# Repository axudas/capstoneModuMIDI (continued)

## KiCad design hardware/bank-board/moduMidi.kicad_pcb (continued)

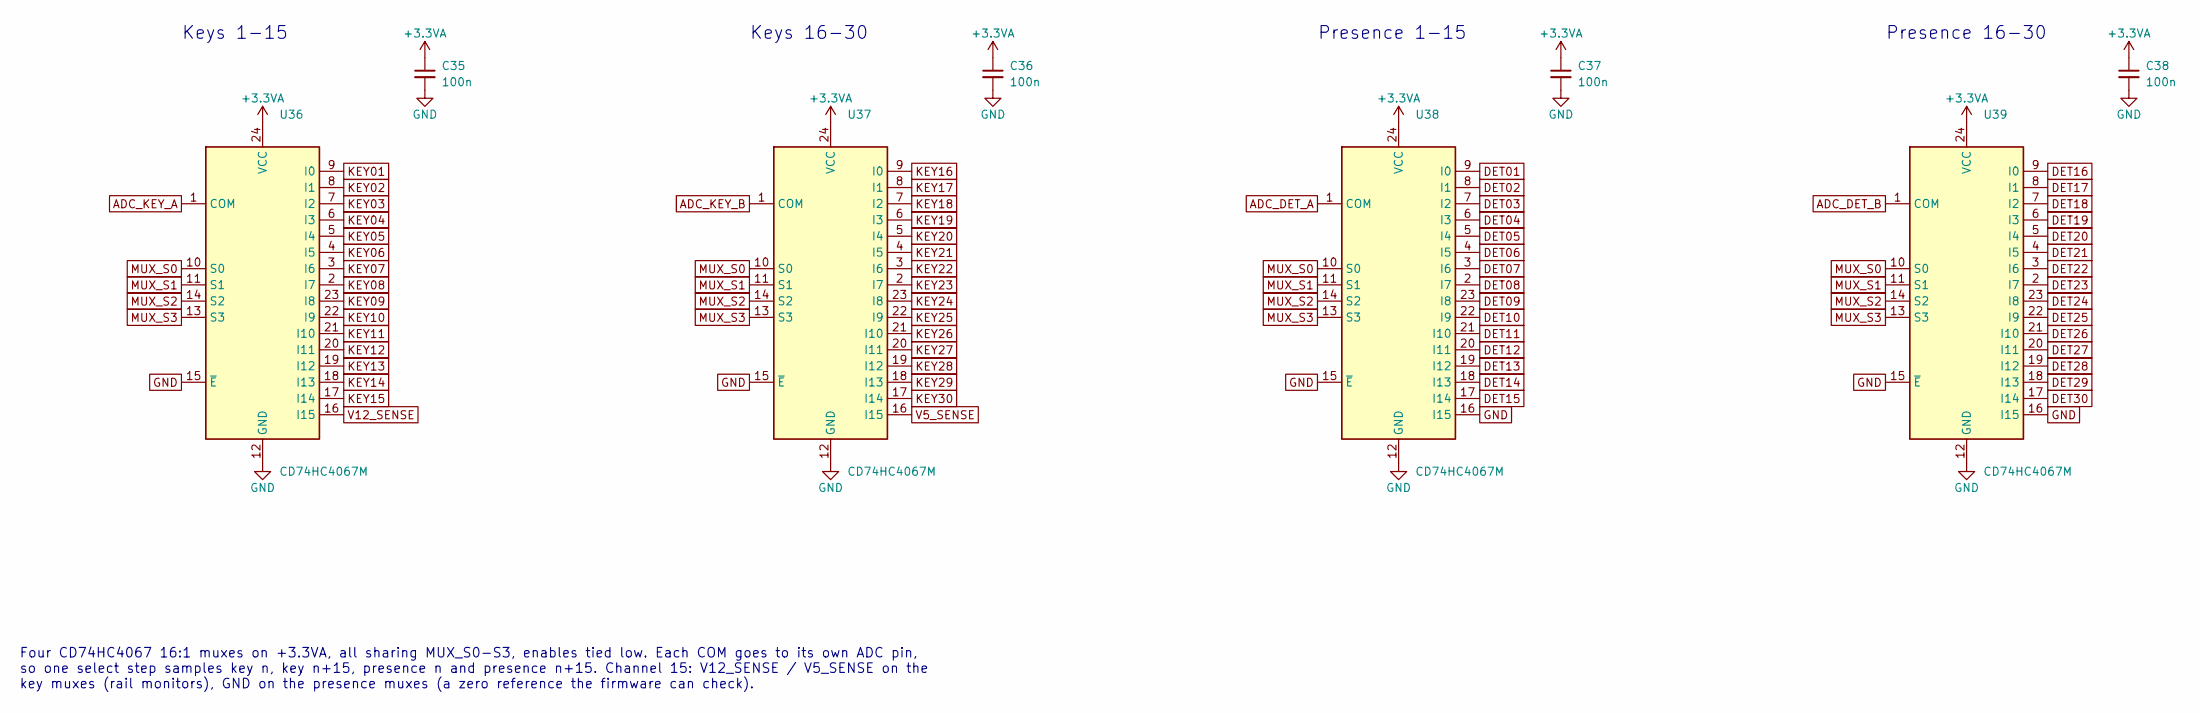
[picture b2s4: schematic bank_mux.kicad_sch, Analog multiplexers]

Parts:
C35, C36, C37, C38: 100n; C_0402_1005Metric
U36, U37, U38, U39: CD74HC4067M; SOIC-24W_7.5x15.4mm_P1.27mm

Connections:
+3.3VA: C35.1, C36.1, C37.1, C38.1, U36.24 (VCC), U37.24 (VCC), U38.24 (VCC), U39.24 (VCC); also elsewhere on the board
ADC_DET_A: U38.1 (COM); also elsewhere on the board
ADC_DET_B: U39.1 (COM); also elsewhere on the board
ADC_KEY_A: U36.1 (COM); also elsewhere on the board
ADC_KEY_B: U37.1 (COM); also elsewhere on the board
DET01: U38.9 (I0); also elsewhere on the board
DET02: U38.8 (I1); also elsewhere on the board
DET03: U38.7 (I2); also elsewhere on the board
DET04: U38.6 (I3); also elsewhere on the board
DET05: U38.5 (I4); also elsewhere on the board
DET06: U38.4 (I5); also elsewhere on the board
DET07: U38.3 (I6); also elsewhere on the board
DET08: U38.2 (I7); also elsewhere on the board
DET09: U38.23 (I8); also elsewhere on the board
DET10: U38.22 (I9); also elsewhere on the board
DET11: U38.21 (I10); also elsewhere on the board
DET12: U38.20 (I11); also elsewhere on the board
DET13: U38.19 (I12); also elsewhere on the board
DET14: U38.18 (I13); also elsewhere on the board
DET15: U38.17 (I14); also elsewhere on the board
DET16: U39.9 (I0); also elsewhere on the board
DET17: U39.8 (I1); also elsewhere on the board
DET18: U39.7 (I2); also elsewhere on the board
DET19: U39.6 (I3); also elsewhere on the board
DET20: U39.5 (I4); also elsewhere on the board
DET21: U39.4 (I5); also elsewhere on the board
DET22: U39.3 (I6); also elsewhere on the board
DET23: U39.2 (I7); also elsewhere on the board
DET24: U39.23 (I8); also elsewhere on the board
DET25: U39.22 (I9); also elsewhere on the board
DET26: U39.21 (I10); also elsewhere on the board
DET27: U39.20 (I11); also elsewhere on the board
DET28: U39.19 (I12); also elsewhere on the board
DET29: U39.18 (I13); also elsewhere on the board
DET30: U39.17 (I14); also elsewhere on the board
GND: C35.2, C36.2, C37.2, C38.2, U36.12 (GND), U36.15 (~E), U37.12 (GND), U37.15 (~E), U38.12 (GND), U38.15 (~E), U38.16 (I15), U39.12 (GND), U39.15 (~E), U39.16 (I15); also elsewhere on the board
KEY01: U36.9 (I0); also elsewhere on the board
KEY02: U36.8 (I1); also elsewhere on the board
KEY03: U36.7 (I2); also elsewhere on the board
KEY04: U36.6 (I3); also elsewhere on the board
KEY05: U36.5 (I4); also elsewhere on the board
KEY06: U36.4 (I5); also elsewhere on the board
KEY07: U36.3 (I6); also elsewhere on the board
KEY08: U36.2 (I7); also elsewhere on the board
KEY09: U36.23 (I8); also elsewhere on the board
KEY10: U36.22 (I9); also elsewhere on the board
KEY11: U36.21 (I10); also elsewhere on the board
KEY12: U36.20 (I11); also elsewhere on the board
KEY13: U36.19 (I12); also elsewhere on the board
KEY14: U36.18 (I13); also elsewhere on the board
KEY15: U36.17 (I14); also elsewhere on the board
KEY16: U37.9 (I0); also elsewhere on the board
KEY17: U37.8 (I1); also elsewhere on the board
KEY18: U37.7 (I2); also elsewhere on the board
KEY19: U37.6 (I3); also elsewhere on the board
KEY20: U37.5 (I4); also elsewhere on the board
KEY21: U37.4 (I5); also elsewhere on the board
KEY22: U37.3 (I6); also elsewhere on the board
KEY23: U37.2 (I7); also elsewhere on the board
KEY24: U37.23 (I8); also elsewhere on the board
KEY25: U37.22 (I9); also elsewhere on the board
KEY26: U37.21 (I10); also elsewhere on the board
KEY27: U37.20 (I11); also elsewhere on the board
KEY28: U37.19 (I12); also elsewhere on the board
KEY29: U37.18 (I13); also elsewhere on the board
KEY30: U37.17 (I14); also elsewhere on the board
MUX_S0: U36.10 (S0), U37.10 (S0), U38.10 (S0), U39.10 (S0); also elsewhere on the board
MUX_S1: U36.11 (S1), U37.11 (S1), U38.11 (S1), U39.11 (S1); also elsewhere on the board
MUX_S2: U36.14 (S2), U37.14 (S2), U38.14 (S2), U39.14 (S2); also elsewhere on the board
MUX_S3: U36.13 (S3), U37.13 (S3), U38.13 (S3), U39.13 (S3); also elsewhere on the board
V5_SENSE: U37.16 (I15); also elsewhere on the board
V12_SENSE: U36.16 (I15); also elsewhere on the board

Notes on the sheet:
Keys 1-15
Keys 16-30
Presence 1-15
Presence 16-30
Four CD74HC4067 16:1 muxes on +3.3VA, all sharing MUX_S0-S3, enables tied low. Each COM goes to its own ADC pin, so one select step samples key n, key n+15, presence n and presence n+15. Channel 15: V12_SENSE / V5_SENSE on the key muxes (rail monitors), GND on the presence muxes (a zero reference t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

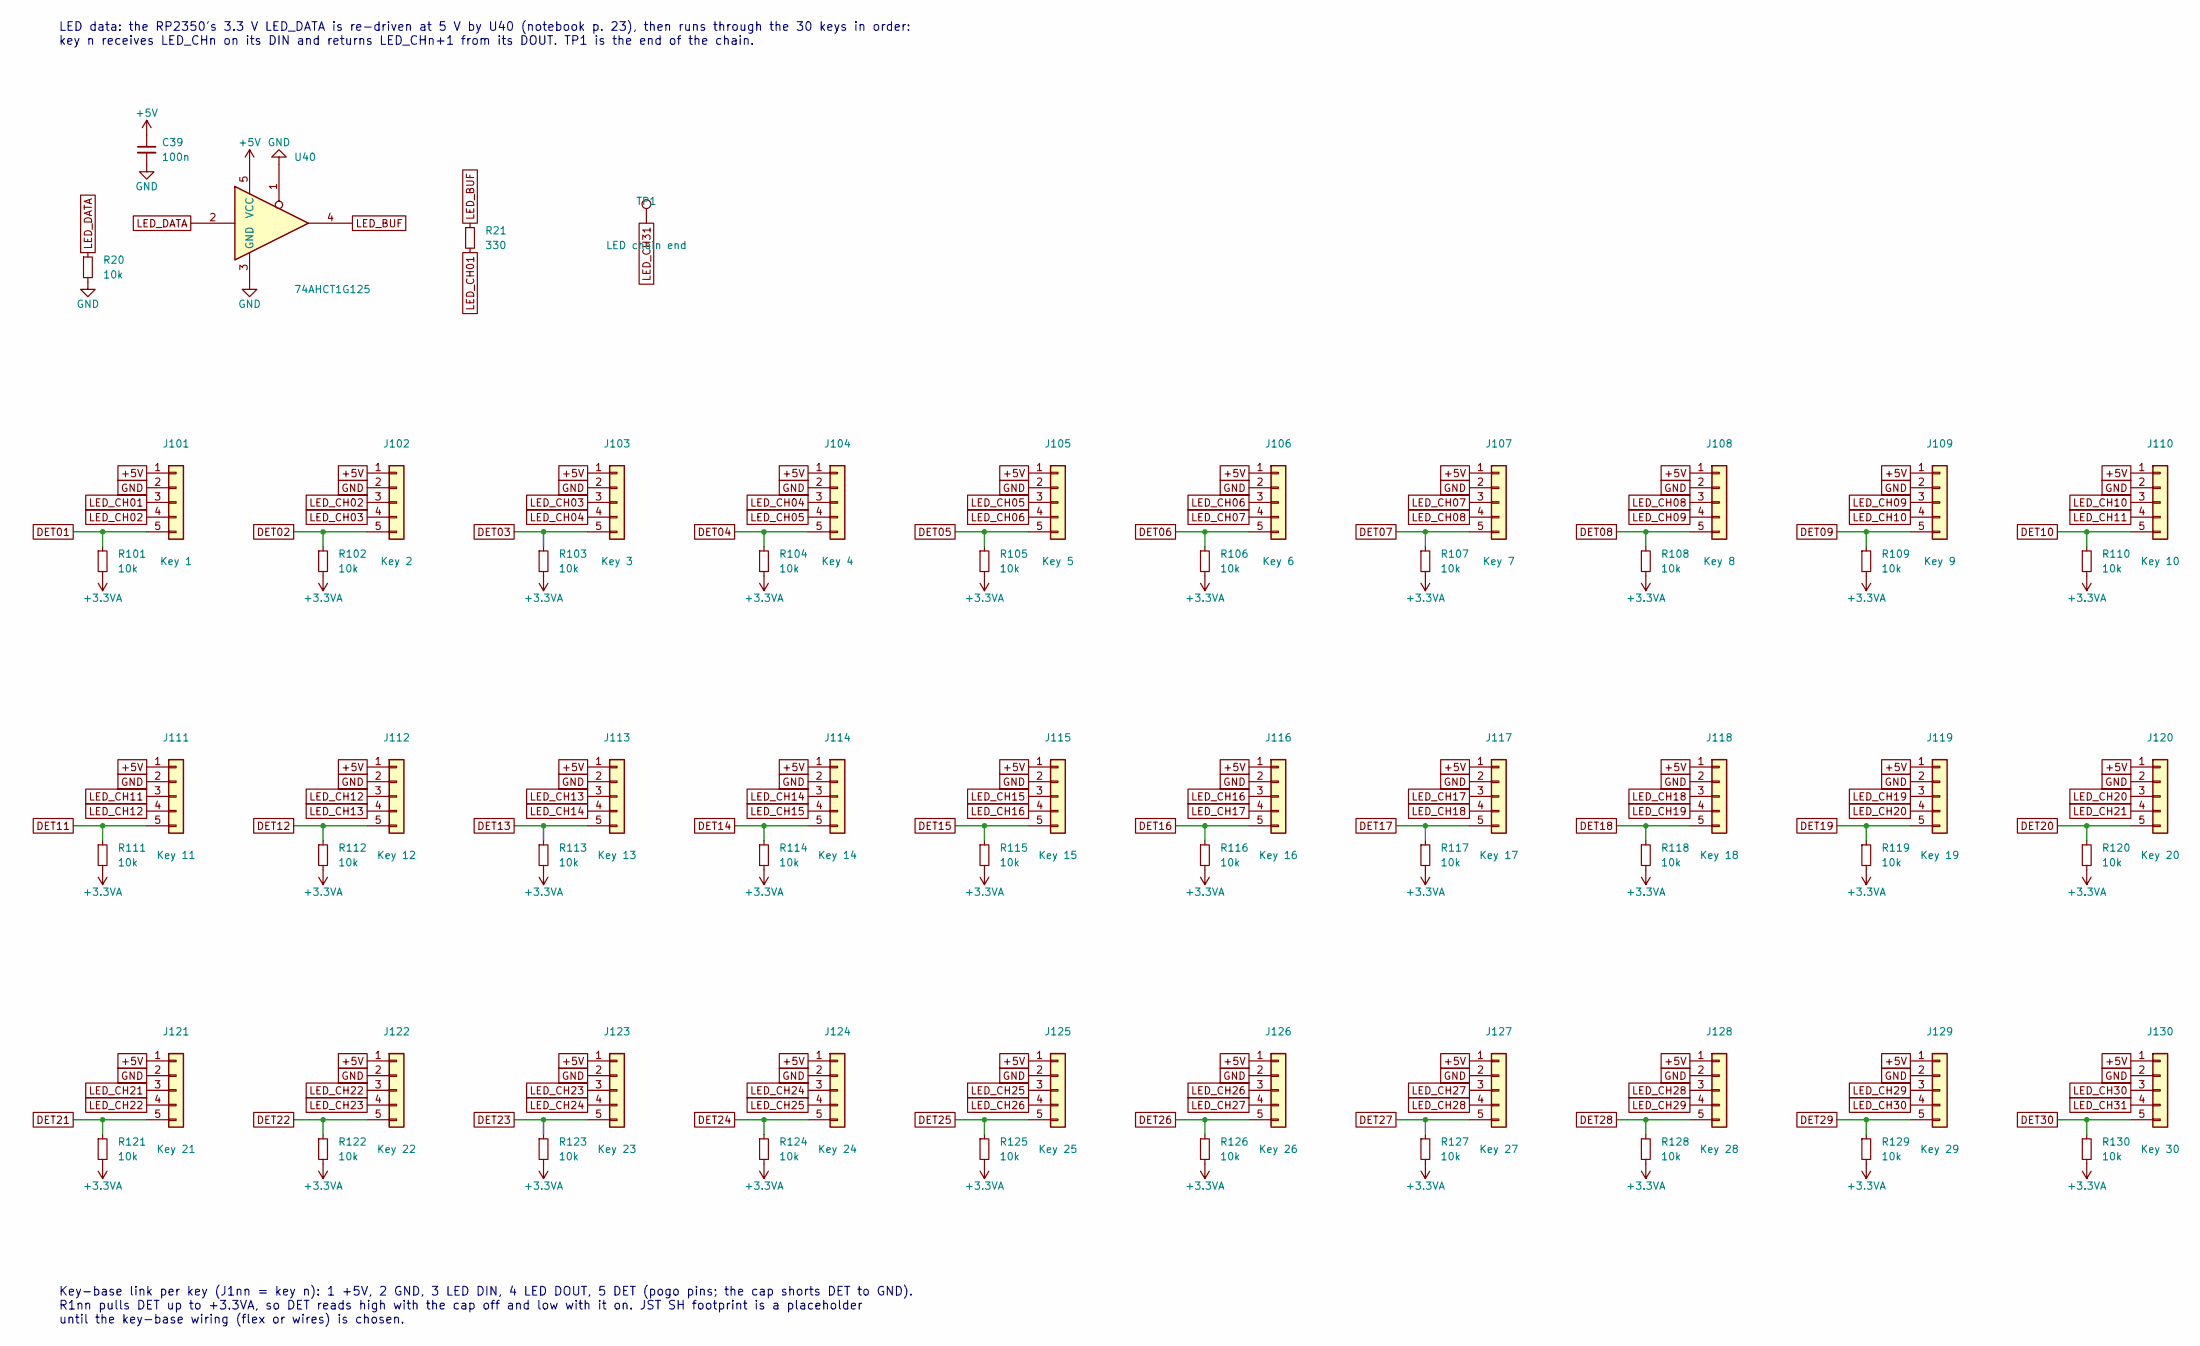
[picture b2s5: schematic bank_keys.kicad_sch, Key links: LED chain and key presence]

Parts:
C39: 100n; C_0402_1005Metric
J101: Key 1; JST_SH_BM05B-SRSS-TB_1x05-1MP_P1.00mm_Vertical
J102: Key 2; JST_SH_BM05B-SRSS-TB_1x05-1MP_P1.00mm_Vertical
J103: Key 3; JST_SH_BM05B-SRSS-TB_1x05-1MP_P1.00mm_Vertical
J104: Key 4; JST_SH_BM05B-SRSS-TB_1x05-1MP_P1.00mm_Vertical
J105: Key 5; JST_SH_BM05B-SRSS-TB_1x05-1MP_P1.00mm_Vertical
J106: Key 6; JST_SH_BM05B-SRSS-TB_1x05-1MP_P1.00mm_Vertical
J107: Key 7; JST_SH_BM05B-SRSS-TB_1x05-1MP_P1.00mm_Vertical
J108: Key 8; JST_SH_BM05B-SRSS-TB_1x05-1MP_P1.00mm_Vertical
J109: Key 9; JST_SH_BM05B-SRSS-TB_1x05-1MP_P1.00mm_Vertical
J110: Key 10; JST_SH_BM05B-SRSS-TB_1x05-1MP_P1.00mm_Vertical
J111: Key 11; JST_SH_BM05B-SRSS-TB_1x05-1MP_P1.00mm_Vertical
J112: Key 12; JST_SH_BM05B-SRSS-TB_1x05-1MP_P1.00mm_Vertical
J113: Key 13; JST_SH_BM05B-SRSS-TB_1x05-1MP_P1.00mm_Vertical
J114: Key 14; JST_SH_BM05B-SRSS-TB_1x05-1MP_P1.00mm_Vertical
J115: Key 15; JST_SH_BM05B-SRSS-TB_1x05-1MP_P1.00mm_Vertical
J116: Key 16; JST_SH_BM05B-SRSS-TB_1x05-1MP_P1.00mm_Vertical
J117: Key 17; JST_SH_BM05B-SRSS-TB_1x05-1MP_P1.00mm_Vertical
J118: Key 18; JST_SH_BM05B-SRSS-TB_1x05-1MP_P1.00mm_Vertical
J119: Key 19; JST_SH_BM05B-SRSS-TB_1x05-1MP_P1.00mm_Vertical
J120: Key 20; JST_SH_BM05B-SRSS-TB_1x05-1MP_P1.00mm_Vertical
J121: Key 21; JST_SH_BM05B-SRSS-TB_1x05-1MP_P1.00mm_Vertical
J122: Key 22; JST_SH_BM05B-SRSS-TB_1x05-1MP_P1.00mm_Vertical
J123: Key 23; JST_SH_BM05B-SRSS-TB_1x05-1MP_P1.00mm_Vertical
J124: Key 24; JST_SH_BM05B-SRSS-TB_1x05-1MP_P1.00mm_Vertical
J125: Key 25; JST_SH_BM05B-SRSS-TB_1x05-1MP_P1.00mm_Vertical
J126: Key 26; JST_SH_BM05B-SRSS-TB_1x05-1MP_P1.00mm_Vertical
J127: Key 27; JST_SH_BM05B-SRSS-TB_1x05-1MP_P1.00mm_Vertical
J128: Key 28; JST_SH_BM05B-SRSS-TB_1x05-1MP_P1.00mm_Vertical
J129: Key 29; JST_SH_BM05B-SRSS-TB_1x05-1MP_P1.00mm_Vertical
J130: Key 30; JST_SH_BM05B-SRSS-TB_1x05-1MP_P1.00mm_Vertical
R20, R101, R102, R103, R104, R105, R106, R107, R108, R109, R110, R111, R112, R113, R114, R115, R116, R117, R118, R119, R120, R121, R122, R123, R124, R125, R126, R127, R128, R129, R130: 10k; R_0402_1005Metric
R21: 330; R_0402_1005Metric
TP1: LED chain end; TestPoint_Pad_D1.0mm
U40: 74AHCT1G125; SOT-23-5

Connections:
+3.3VA: R101.2, R102.2, R103.2, R104.2, R105.2, R106.2, R107.2, R108.2, R109.2, R110.2, R111.2, R112.2, R113.2, R114.2, R115.2, R116.2, R117.2, R118.2, R119.2, R120.2, R121.2, R122.2, R123.2, R124.2, R125.2, R126.2, R127.2, R128.2, R129.2, R130.2; also elsewhere on the board
+5V: C39.1, J101.1, J102.1, J103.1, J104.1, J105.1, J106.1, J107.1, J108.1, J109.1, J110.1, J111.1, J112.1, J113.1, J114.1, J115.1, J116.1, J117.1, J118.1, J119.1, J120.1, J121.1, J122.1, J123.1, J124.1, J125.1, J126.1, J127.1, J128.1, J129.1, J130.1, U40.5 (VCC); also elsewhere on the board
DET01: J101.5, R101.1; also elsewhere on the board
DET02: J102.5, R102.1; also elsewhere on the board
DET03: J103.5, R103.1; also elsewhere on the board
DET04: J104.5, R104.1; also elsewhere on the board
DET05: J105.5, R105.1; also elsewhere on the board
DET06: J106.5, R106.1; also elsewhere on the board
DET07: J107.5, R107.1; also elsewhere on the board
DET08: J108.5, R108.1; also elsewhere on the board
DET09: J109.5, R109.1; also elsewhere on the board
DET10: J110.5, R110.1; also elsewhere on the board
DET11: J111.5, R111.1; also elsewhere on the board
DET12: J112.5, R112.1; also elsewhere on the board
DET13: J113.5, R113.1; also elsewhere on the board
DET14: J114.5, R114.1; also elsewhere on the board
DET15: J115.5, R115.1; also elsewhere on the board
DET16: J116.5, R116.1; also elsewhere on the board
DET17: J117.5, R117.1; also elsewhere on the board
DET18: J118.5, R118.1; also elsewhere on the board
DET19: J119.5, R119.1; also elsewhere on the board
DET20: J120.5, R120.1; also elsewhere on the board
DET21: J121.5, R121.1; also elsewhere on the board
DET22: J122.5, R122.1; also elsewhere on the board
DET23: J123.5, R123.1; also elsewhere on the board
DET24: J124.5, R124.1; also elsewhere on the board
DET25: J125.5, R125.1; also elsewhere on the board
DET26: J126.5, R126.1; also elsewhere on the board
DET27: J127.5, R127.1; also elsewhere on the board
DET28: J128.5, R128.1; also elsewhere on the board
DET29: J129.5, R129.1; also elsewhere on the board
DET30: J130.5, R130.1; also elsewhere on the board
GND: C39.2, J101.2, J102.2, J103.2, J104.2, J105.2, J106.2, J107.2, J108.2, J109.2, J110.2, J111.2, J112.2, J113.2, J114.2, J115.2, J116.2, J117.2, J118.2, J119.2, J120.2, J121.2, J122.2, J123.2, J124.2, J125.2, J126.2, J127.2, J128.2, J129.2, J130.2, R20.2, U40.1, U40.3 (GND); also elsewhere on the board
LED_BUF: R21.1, U40.4
LED_CH01: J101.3, R21.2
LED_CH02: J101.4, J102.3
LED_CH03: J102.4, J103.3
LED_CH04: J103.4, J104.3
LED_CH05: J104.4, J105.3
LED_CH06: J105.4, J106.3
LED_CH07: J106.4, J107.3
LED_CH08: J107.4, J108.3
LED_CH09: J108.4, J109.3
LED_CH10: J109.4, J110.3
LED_CH11: J110.4, J111.3
LED_CH12: J111.4, J112.3
LED_CH13: J112.4, J113.3
LED_CH14: J113.4, J114.3
LED_CH15: J114.4, J115.3
LED_CH16: J115.4, J116.3
LED_CH17: J116.4, J117.3
LED_CH18: J117.4, J118.3
LED_CH19: J118.4, J119.3
LED_CH20: J119.4, J120.3
LED_CH21: J120.4, J121.3
LED_CH22: J121.4, J122.3
LED_CH23: J122.4, J123.3
LED_CH24: J123.4, J124.3
LED_CH25: J124.4, J125.3
LED_CH26: J125.4, J126.3
LED_CH27: J126.4, J127.3
LED_CH28: J127.4, J128.3
LED_CH29: J128.4, J129.3
LED_CH30: J129.4, J130.3
LED_CH31: J130.4, TP1.1
LED_DATA: R20.1, U40.2; also elsewhere on the board

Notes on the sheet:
LED data: the RP2350's 3.3 V LED_DATA is re-driven at 5 V by U40 (notebook p. 23), then runs through the 30 keys in order: key n receives LED_CHn on its DIN and returns LED_CHn+1 from its DOUT. TP1 is the end of the chain.
Key-base link per key (J1nn = key n): 1 +5V, 2 GND, 3 LED DIN, 4 LED DOUT, 5 DET (pogo pins; the cap shorts DET to GND). R1nn pulls DET up to +3.3VA, so DET reads high with the cap off and low with it on. JST SH footprint is a placeholder until the key-base wiring (flex or wires) is chosen.

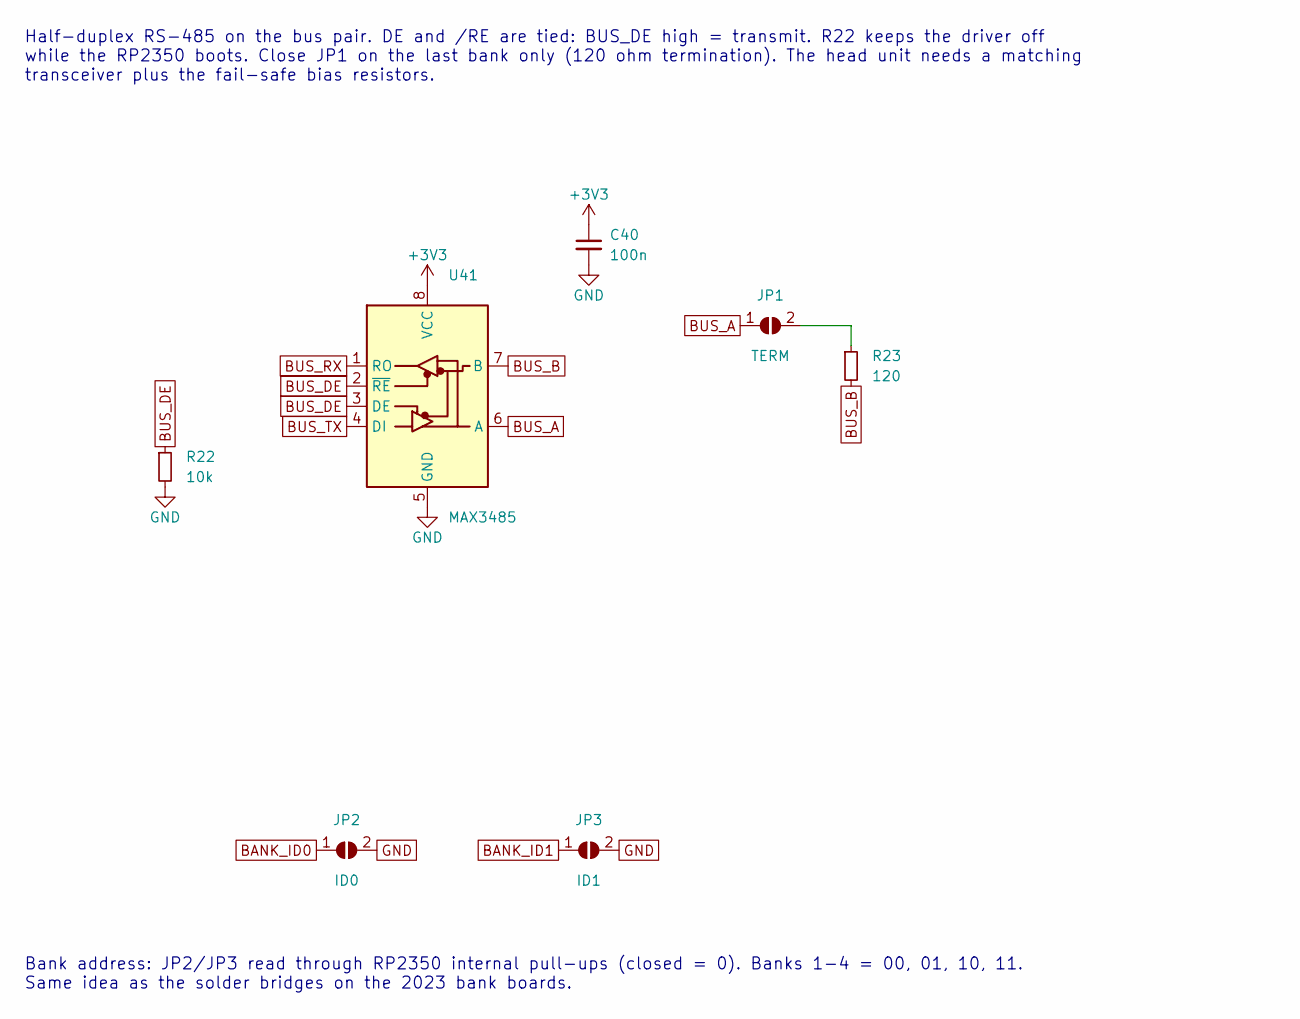
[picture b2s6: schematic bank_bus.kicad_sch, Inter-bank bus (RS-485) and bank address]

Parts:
C40: 100n; C_0402_1005Metric
JP1: TERM; SolderJumper-2_P1.3mm_Open_RoundedPad1.0x1.5mm
JP2: ID0; SolderJumper-2_P1.3mm_Open_RoundedPad1.0x1.5mm
JP3: ID1; SolderJumper-2_P1.3mm_Open_RoundedPad1.0x1.5mm
R22: 10k; R_0402_1005Metric
R23: 120; R_0603_1608Metric
U41: MAX3485; SOIC-8_3.9x4.9mm_P1.27mm

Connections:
+3V3: C40.1, U41.8 (VCC); also elsewhere on the board
BANK_ID0: JP2.1 (A); also elsewhere on the board
BANK_ID1: JP3.1 (A); also elsewhere on the board
BUS_A: JP1.1 (A), U41.6 (A); also elsewhere on the board
BUS_B: R23.2, U41.7 (B); also elsewhere on the board
BUS_DE: R22.1, U41.2 (~RE), U41.3 (DE); also elsewhere on the board
BUS_RX: U41.1 (RO); also elsewhere on the board
BUS_TX: U41.4 (DI); also elsewhere on the board
GND: C40.2, JP2.2 (B), JP3.2 (B), R22.2, U41.5 (GND); also elsewhere on the board
unnamed: JP1.2 (B), R23.1

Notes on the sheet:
Half-duplex RS-485 on the bus pair. DE and /RE are tied: BUS_DE high = transmit. R22 keeps the driver off while the RP2350 boots. Close JP1 on the last bank only (120 ohm termination). The head unit needs a matching transceiver plus the fail-safe bias resistors.
Bank address: JP2/JP3 read through RP2350 internal pull-ups (closed = 0). Banks 1-4 = 00, 01, 10, 11. Same idea as the solder bridges on the 2023 bank boards.

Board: 2 copper layers, 220 parts (124 on the bottom side), 148 nets, no tracks yet.

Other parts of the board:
H1, H2, H3, H4, H5, H6: M2; MountingHole_2.2mm_M2
